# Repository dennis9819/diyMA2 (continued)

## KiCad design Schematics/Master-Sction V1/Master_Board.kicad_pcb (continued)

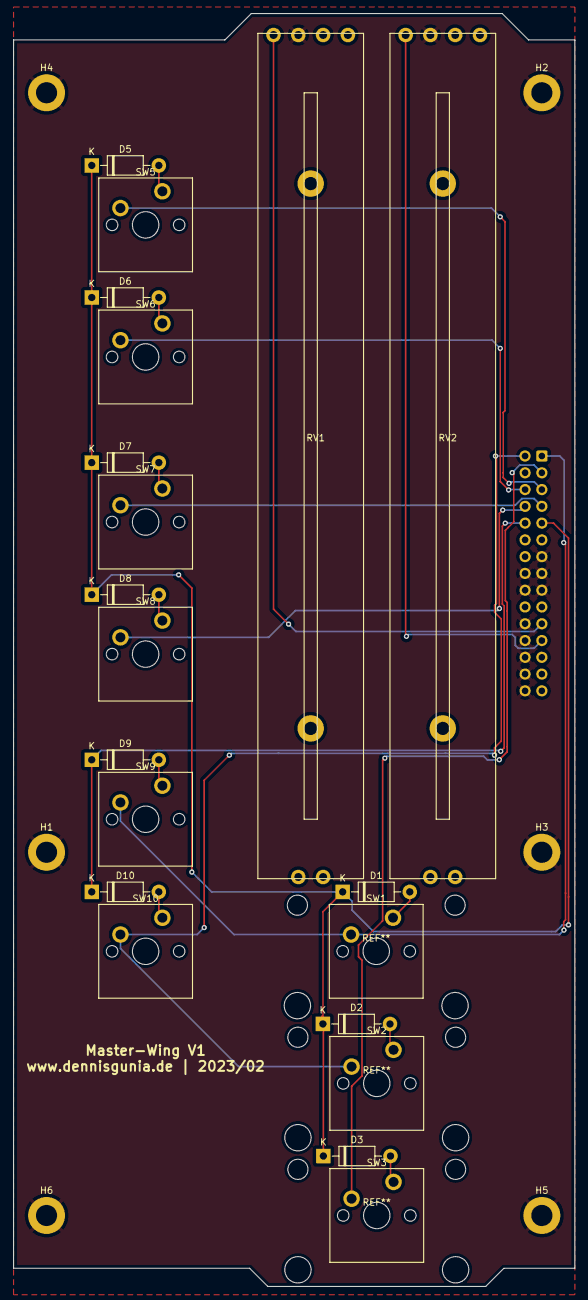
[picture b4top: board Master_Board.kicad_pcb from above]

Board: 2 copper layers, 85.0 x 192.8 mm, 27 parts (1 on the bottom side), 22 nets.

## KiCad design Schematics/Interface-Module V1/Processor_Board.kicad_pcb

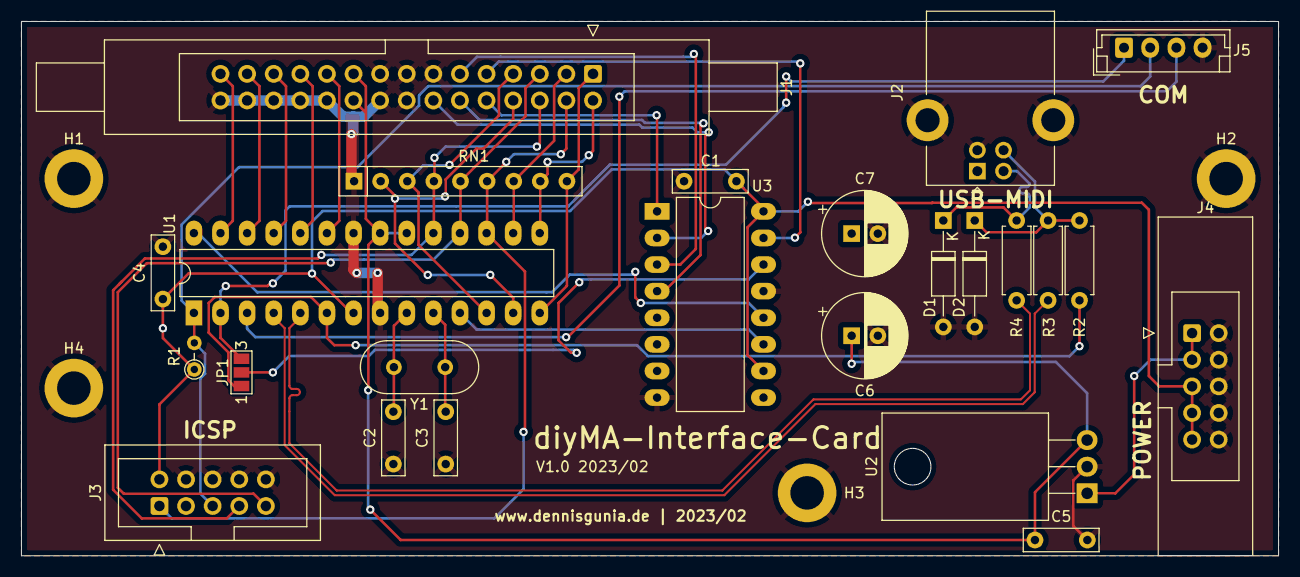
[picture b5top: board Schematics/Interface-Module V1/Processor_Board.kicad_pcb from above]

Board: 2 copper layers, 120.0 x 51.0 mm, 28 parts (0 on the bottom side), 35 nets.

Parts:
C1, C4, C5: 100nF; C_Rect_L7.0mm_W2.0mm_P5.00mm
C2, C3: 33pF; C_Rect_L7.0mm_W2.0mm_P5.00mm
C6, C7: 100uF; CP_Radial_D8.0mm_P2.50mm
D1, D2: 3V6; D_DO-35_SOD27_P10.16mm_Horizontal
H1, H2, H3, H4: MountingHole; MountingHole_3.2mm_M3_DIN965_Pad
J1: Conn_02x16_Odd_Even; IDC-Header_2x15_P2.54mm_Latch6.5mm_Vertical
J2: USB_B; USB_B_Lumberg_2411_02_Horizontal
J3: Conn_02x05_Odd_Even; IDC-Header_2x05_P2.54mm_Vertical
J4: Conn_02x05_Odd_Even; IDC-Header_2x05_P2.54mm_Latch_Vertical
J5: Conn_01x04_Male; JST_EH_B4B-EH-A_1x04_P2.50mm_Vertical
JP1: Jumper_3_Open; SolderJumper-3_P1.3mm_Open_Pad1.0x1.5mm_NumberLabels
R1: 10k; R_Axial_DIN0204_L3.6mm_D1.6mm_P2.54mm_Vertical
R2: 2k2; R_Axial_DIN0207_L6.3mm_D2.5mm_P7.62mm_Horizontal
R3, R4: 68; R_Axial_DIN0207_L6.3mm_D2.5mm_P7.62mm_Horizontal
RN1: R_Network08; R_Array_SIP9
U1: ATmega8-16P; DIP-28_W7.62mm_LongPads
U2: L7805; TO-220-3_Horizontal_TabDown
U3: 74HC595; DIP-16_W10.16mm_LongPads
Y1: 16MHz; Crystal_HC18-U_Vertical

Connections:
+5V: C1.1, C4.1, C7.1, J3.2, J4.5, J4.7, J4.9, R1.1, U1.7 (VCC), U3.10 (~SRCLR), U3.16 (VCC)
+5VA: C5.1, C6.1, J1.19, J1.20, U1.20 (AVCC), U1.21 (AREF), U2.3 (OUT)
+12V: J4.1, J4.3, U2.1 (IN)
/#USB_D+: D2.1 (K), J2.3 (D+), R2.1, R3.1
/#USB_D-: D1.1 (K), J2.2 (D-), R4.1
ANALOG_1: J1.21, U1.23 (PC0)
ANALOG_2: J1.23, U1.24 (PC1)
ANALOG_3: J1.25, U1.25 (PC2)
ANALOG_4: J1.27, U1.26 (PC3)
ANALOG_5: J1.29, U1.27 (PC4)
GND: C1.2, C2.1, C3.1, C4.2, C5.2, C6.2, C7.2, D1.2 (A), D2.2 (A), H1.1, H2.1, H3.1, H4.1, J1.13, J1.15, J1.16, J1.17, J1.18, J1.22, J1.24, J1.26, J1.28, J1.30, J2.4 (GND), J2.5 (Shield), J3.4, J3.6, J3.8, J3.10, J4.2, J4.4, J4.6, J4.8, J4.10, J5.4, RN1.1 (common), U1.8 (GND), U1.22 (AGND), U2.2 (GND), U3.8 (GND), U3.13 (~OE)
ICSP_MISO: J1.5, J3.9, RN1.5 (R4), U1.18 (PB4)
ICSP_MOSI: J1.4, J3.1, RN1.6 (R5), U1.17 (PB3)
ICSP_SCK: J1.6, J3.7, RN1.4 (R3), U1.19 (PB5)
MATRIX_1: J1.1, RN1.9 (R8), U1.14 (PB0)
MATRIX_2: J1.2, RN1.8 (R7), U1.15 (PB1)
MATRIX_3: J1.3, RN1.7 (R6), U1.16 (PB2)
MATRIX_7: J1.7, RN1.3 (R2), U1.12 (PD6)
MATRIX_8: J1.8, RN1.2 (R1), U1.13 (PD7)
MATRIX_A: J1.9, U3.15 (QA)
MATRIX_B: J1.10, U3.1 (QB)
MATRIX_C: J1.14, U3.2 (QC)
MATRIX_D: J1.11, U3.3 (QD)
MATRIX_E: J1.12, U3.4 (QE)
unnamed: C2.2, U1.9 (PB6/XTAL1), Y1.2
unnamed: C3.2, U1.10 (PB7/XTAL2), Y1.1
unnamed: JP1.2 (C), U3.14 (SER)
unnamed: U1.11 (PD5), U3.11 (SRCLK)
unnamed: U1.28 (PC5), U3.12 (RCLK)
RS232_RX/SER: J5.1, JP1.3 (B), U1.2 (PD0)
RS232_TX: J5.3, U1.3 (PD1)
USB_D+: R3.2, U1.4 (PD2)
USB_D-: R4.2, U1.5 (PD3)
USB_INT/SER: JP1.1 (A), R2.2, U1.6 (PD4)
~RESET: J3.5, J5.2, R1.2, U1.1 (PC6/~RESET)

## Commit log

2023-07-05 master init
2023-07-05 cleanup
2025-01-05 Added firmware
2025-01-05 add Readme and Labels
